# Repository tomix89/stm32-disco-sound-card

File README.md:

# stm32-disco-sound-card
An UAC1 implementation for the STM32F411-DISCO board with **tone control**!\
What i wanted to achive a long time for now to have a ligh weight USB DAC for my headphones which does not need any special driver and have hardware physical tone contol in the digital domain.\
For this the STM32F411-DISCO board which i had for years seemed to be a really good candidate with it's CS43L22 audio headphone DAC. The project aims for a generic 48kHz 24bit stereo implementation.\
A quick, short, real life demo of the prototype: https://youtu.be/ILklubHfwOU

This project heavily relyes on the tiny USB project:\
https://docs.tinyusb.org/en/latest \
https://github.com/hathach/tinyusb \
Big thank you for the developers! It is a lot better and in depth impelemntation then the middle ware from STM itself.

The project is made by the STM Cube MX, and programmed in their STM32CubeIDE 2.0.0

There is a hand written tool to calculate the best (exact) configuration for the I2S PLL, as STM cube seemed to not support this
tools\i2s-clock-calc.py

Current state of the prototype:
<table>
  <tr>
    <td>
      
    </td>
    <td>
      
    </td>
  </tr>
  <tr>
    <td colspan="2" align="center">
      
    </td>
  </tr>
</table>

Tested with:\
​  ● Windows 11 25H2 and 23H2\
​  ● Windows 10 22H2\
​  ● Ubuntu  22.04 LTS\
​  ● Android 8.1.0 (Huawei Y5 2018)\
​  ● Android 9 (Xiaomi Redmi 6)\
​  ● Android 12 (Samsung Galaxy A41)\
​  ● Android 8.1.0 (Huawei Y5 2018)\
​  ● Android 9 (Xiaomi Redmi 6)\
​  ● Android 12 (Samsung Galaxy A41)

<br>

Note on how the volume is handled:
- Windows seems to respect that we have a volume control, and sends the full amplitude audio stream and sets the volume by a separate volume value. In this case the DSP can process the audio in full precision, because we are setting the volume only before the DAC
- Ubuntu -> ToDo check
- On all the Android devices I have tried, the volume is set to max on the USB level, and the phone sends the PCM stream scaled to the actual volume

## Hardware
The custom part of the board is designed in KiCad 10.\
Big thanks to the https://www.youtube.com/@HTMWorkshop for the really nice tutorial videos for teaching me KiCad in a few hours.

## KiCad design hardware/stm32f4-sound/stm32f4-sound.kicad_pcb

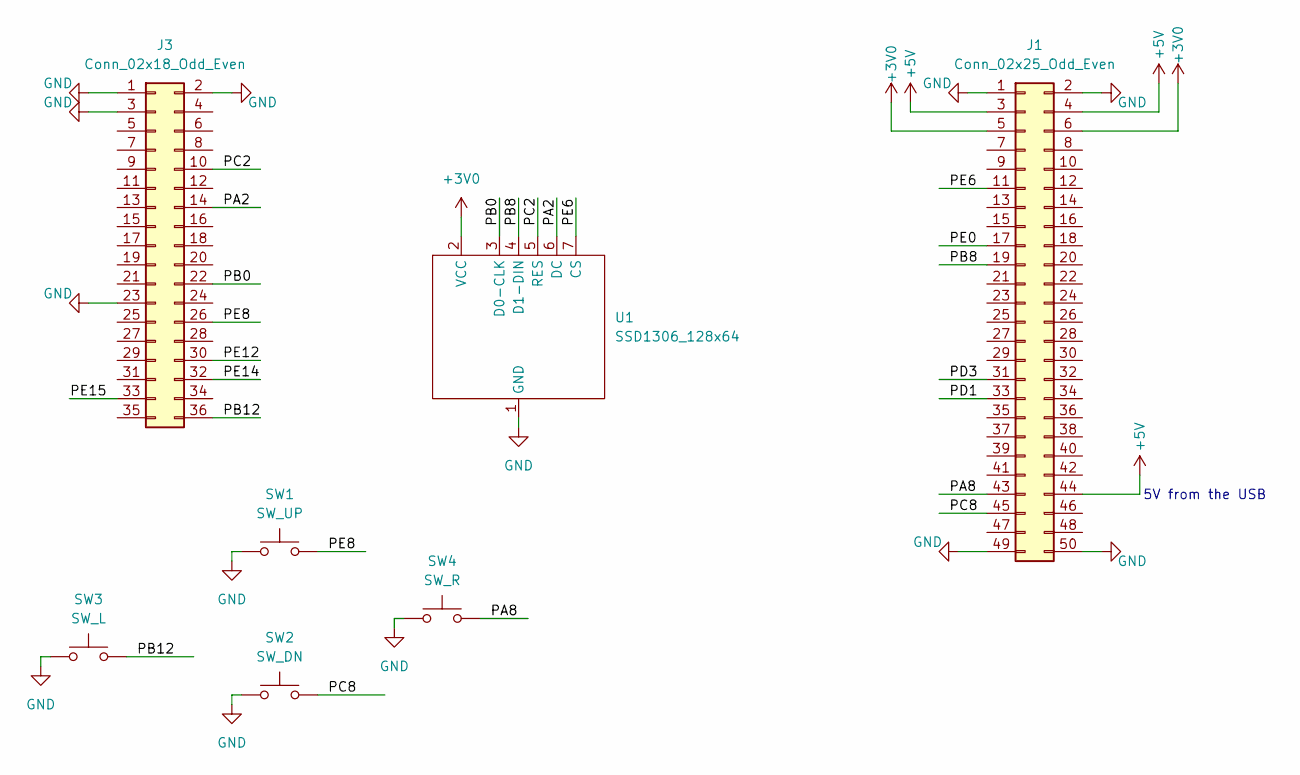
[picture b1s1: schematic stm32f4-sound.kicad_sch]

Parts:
J1: Conn_02x25_Odd_Even; PinSocket_2x25_P2.54mm_Vertical
J3: Conn_02x18_Odd_Even; PinSocket_2x18_P2.54mm_Vertical
SW1: SW_UP; SW_PUSH-12mm
SW2: SW_DN; SW_PUSH-12mm
SW3: SW_L; SW_PUSH-12mm
SW4: SW_R; SW_PUSH-12mm
U1: SSD1306_128x64; SSD1306-SPI

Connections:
+3V0: J1.5, J1.6, U1.2 (VCC)
+5V: J1.3, J1.4, J1.44
/PA2: J3.14, U1.6 (DC)
/PA8: J1.43, SW4.2
/PB0: J3.22, U1.3 (D0-CLK)
/PB8: J1.19, U1.4 (D1-DIN)
/PB12: J3.36, SW3.2
/PC2: J3.10, U1.5 (RES)
/PC8: J1.45, SW2.2
/PD1: J1.33
/PD3: J1.31
/PE0: J1.17
/PE6: J1.11, U1.7 (CS)
/PE8: J3.26, SW1.2
/PE12: J3.30
/PE14: J3.32
/PE15: J3.33
GND: J1.1, J1.2, J1.49, J1.50, J3.1, J3.2, J3.3, J3.23, SW1.1, SW2.1, SW3.1, SW4.1, U1.1 (GND)

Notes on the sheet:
5V from the USB

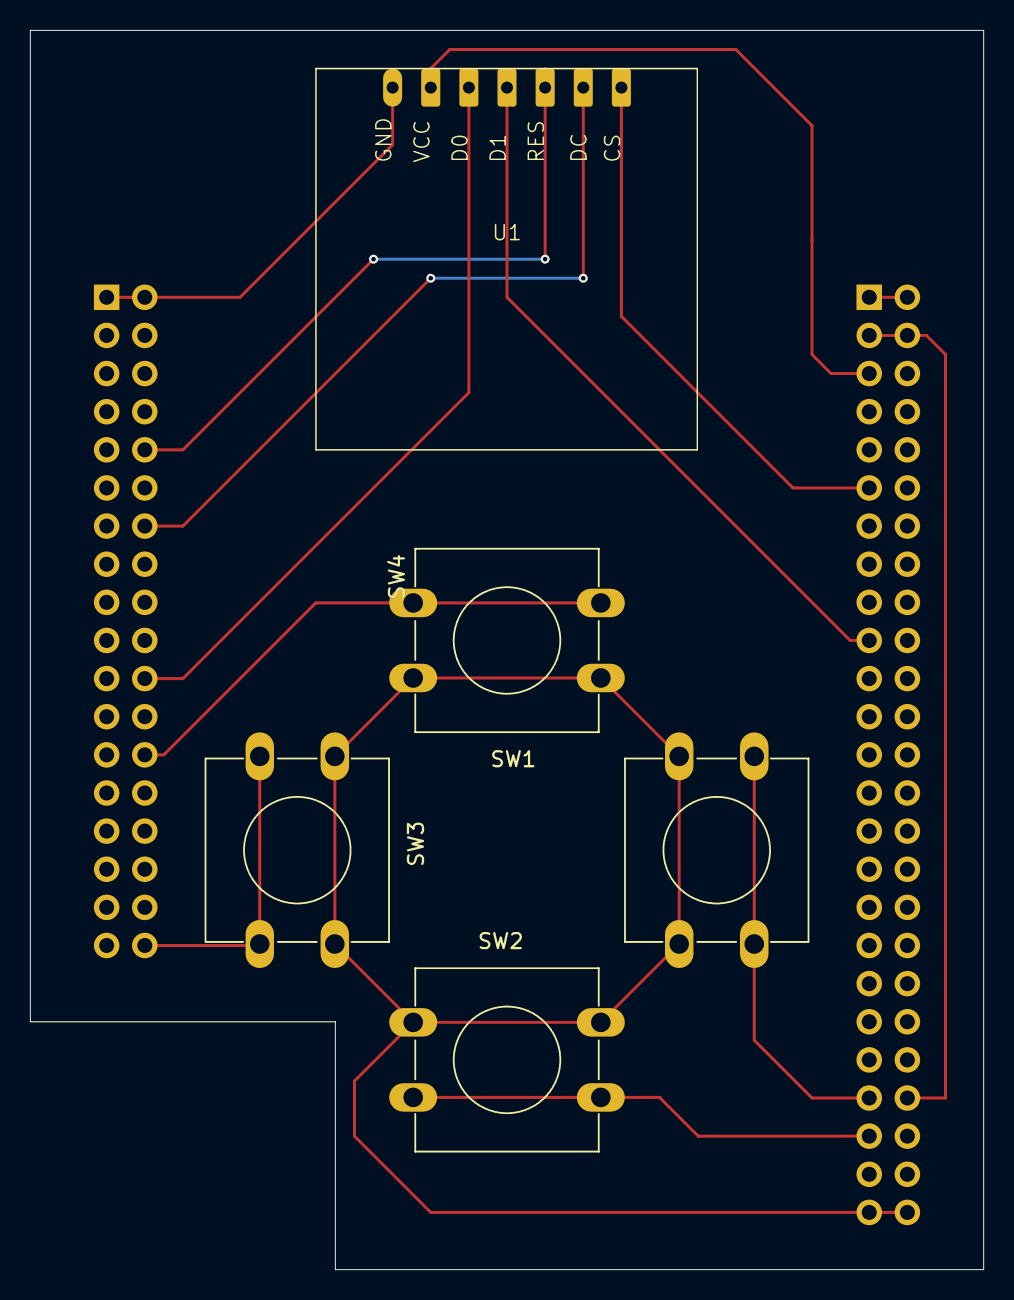
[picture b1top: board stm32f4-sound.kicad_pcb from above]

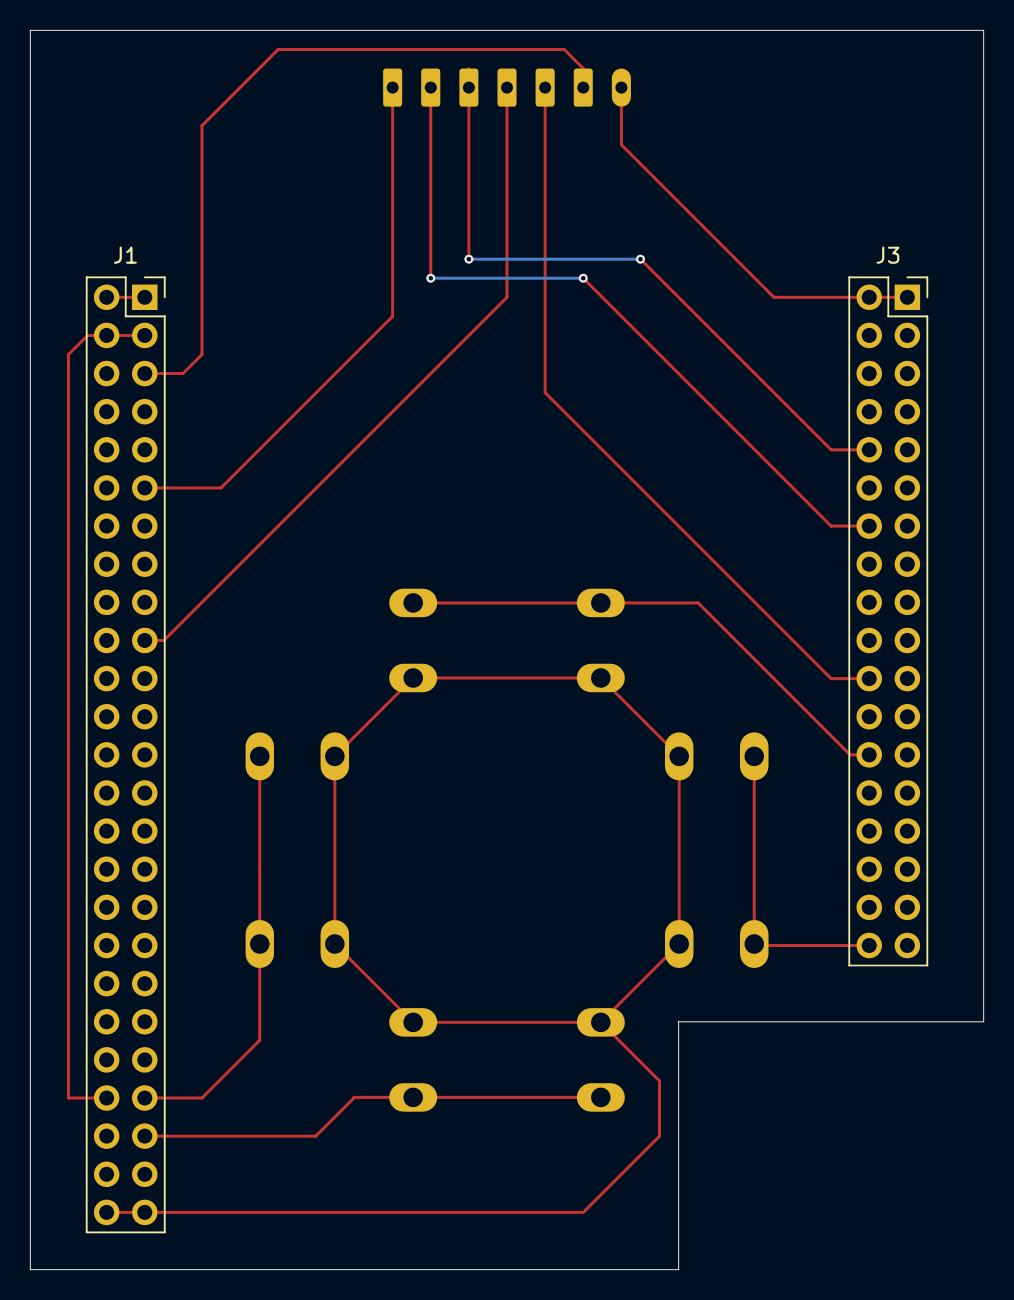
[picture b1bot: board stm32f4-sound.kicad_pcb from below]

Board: 2 copper layers, 63.5 x 82.5 mm, 7 parts (2 on the bottom side), 12 nets.

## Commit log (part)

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2026-02-14 Cube MX generated project with all the needed peripherals initialized
2026-02-14 Added the tiny USB source folder
    - tiny USB version dc00f3536f7f636ffea639430faa2d828317137c
2026-02-14 Added tinyusb-src folder to project
2026-02-14 Added USB UAC related files
2026-02-14 Add more things from the example
2026-02-14 Add the last portion form the example
    - board_delay is not used - delete
2026-02-14 Add some basic control for the CS43L22 audio codec
2026-02-14 final setup to get audio form the heaphone plug
    - start streaming data to ADC when we have some buffer
    - added the I2S DMA callbacks
2026-02-14 fix a compilation warning about board_led_write
2026-02-14 temp fix on noise issue on audio_stop
2026-02-16 Have only 48KHz sample rate
    - added fault handler red LED blinking
    - set the FiFo threshold to 4ms
2026-02-16 Improved start/stop in loadMore()
    - orange led now signalizes the I2S play state
    - blue led is now a really basic signal level meter
2026-02-17 remove unused USB host related code
2026-02-17 Volume control and mute now works
2026-02-20 Added OLED library
    - OLED lib on version f3bd5d0f9e7d314cdf3d9bdac4f0a6278950a1f5
    - added OLED lib files
    - enabled the SPI2
    - enabled DMA1_stream4 for SPI
    - changed LED names to have the colors in them
2026-02-20 Tweak the OLED lib
    - map my GPIO pins
    - get rid of the power on/off
    - pass the SPI2 pointer upon init
    - add the example to test
2026-02-20 OLED is working
    - audio_init() return value is checked
    - SSD1306_Init -> the SSD1306_Clear() was at the wrong place
2026-02-25 Basic menu
    - added user buttons
    - added menu (only dummy for now)
    - OLED SS signal needs to be manual
    - reset the OLED cursor back to 0,0 before sending data
2026-02-25 fully functional basic menu
    - still not wired into the audio codec
2026-02-26 Have the UI screen initialized
    - increased OLED SPI speed - on datasheet max is 25MHz it was OK around 20MHz so with a margin let's do 6MHz
    - update the screen unconditionally - if already ongoing stop DMA
2026-02-26 Tone control is fully working
2026-03-04 Display goes to sleep
    - display turns off after SCREEN_TIMEOUT_MS
    - some renames
    - send the tone control at start
    - SSD1306_CMD_ACCESS() is now part of ssd1306_SPI_WriteCmd()
2026-03-05 Use only master volume, no separate L/R
    - volume and balance are now in audio_controls
    - use percentual scaling on USB instead of real dB
    - set the balance on HW
    - reduced range for volume -102dB is way too much (reduced to -80dB)
2026-03-09 Switch to 24bit audio - DAC side
    - fix audio_set_pcm_mute
    - for now get rid of the signal level indicator blue led
2026-03-09 Switch to 24bit audio - USB side
2026-03-11 optimizing USB read out
2026-04-01 Fix loosing byte sync
    - for some reason one of my PC's on rare occasions sends an incomplete ISO transfer which is not divisible by (2ch * 24bit = 2ch * 3byte) 6byte - fix it by discarding the broken bytes from the FiFo
    - fixed the release build
    - fix the calculation of CFG_TUD_AUDIO_FUNC_1_EP_OUT_SW_BUF_SZ and enlarge it a bit
    - turned off the CFG_AUDIO_DEBUG
2026-04-01 Fix clipping on high tone correction gain
    - decrease the master volume by the tone correction gain
2026-04-22 First steps with the custom PCB
2026-04-23 Remap the OLED pins to fit the HW
    - add 4th user button
2026-04-27 Finalize the PCB
2026-04-28 New 4 button UI
2026-04-28 Remap to 128x64 px
2026-05-07 Add analog gain
